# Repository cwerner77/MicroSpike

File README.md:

# µSpike
An analog spiking neural network (SNN) experiment board with digital control

## Purpose
A powerful and flexible experimental board for exploring SNN technology. This project is primarily aimed at lecturers, students, and researchers at universities.

## Project parts
- Electronics: Schematics and PCB design
- Microcontroller programs usable with https://www.pjrc.com/store/teensy41.html and 
- Circuit simulation usable with https://www.falstad.com/circuit/

## Prerequisites
- Basic knowledge on how SNN work
- Basic skills in hardware-level computer engineering: setting up microcontrollers and attaching sensors as needed
- Basic skills in electrical engineering: use a graphical circuit simulation tool for designing a SNN circuit from predefined building blocks

## Typical workflow
1. Design your SNN in simulation environment
2. Build µSpike board and flash µSpike control software
3. Configure µSpike to your application's needs using the µSpike control software
4. Do your experiments and enjoy µSpike control software's powerful logging features

## Licenses
- All hardware parts: CERN-OHL-P-2.0
- All software parts: Apache-2.0 license

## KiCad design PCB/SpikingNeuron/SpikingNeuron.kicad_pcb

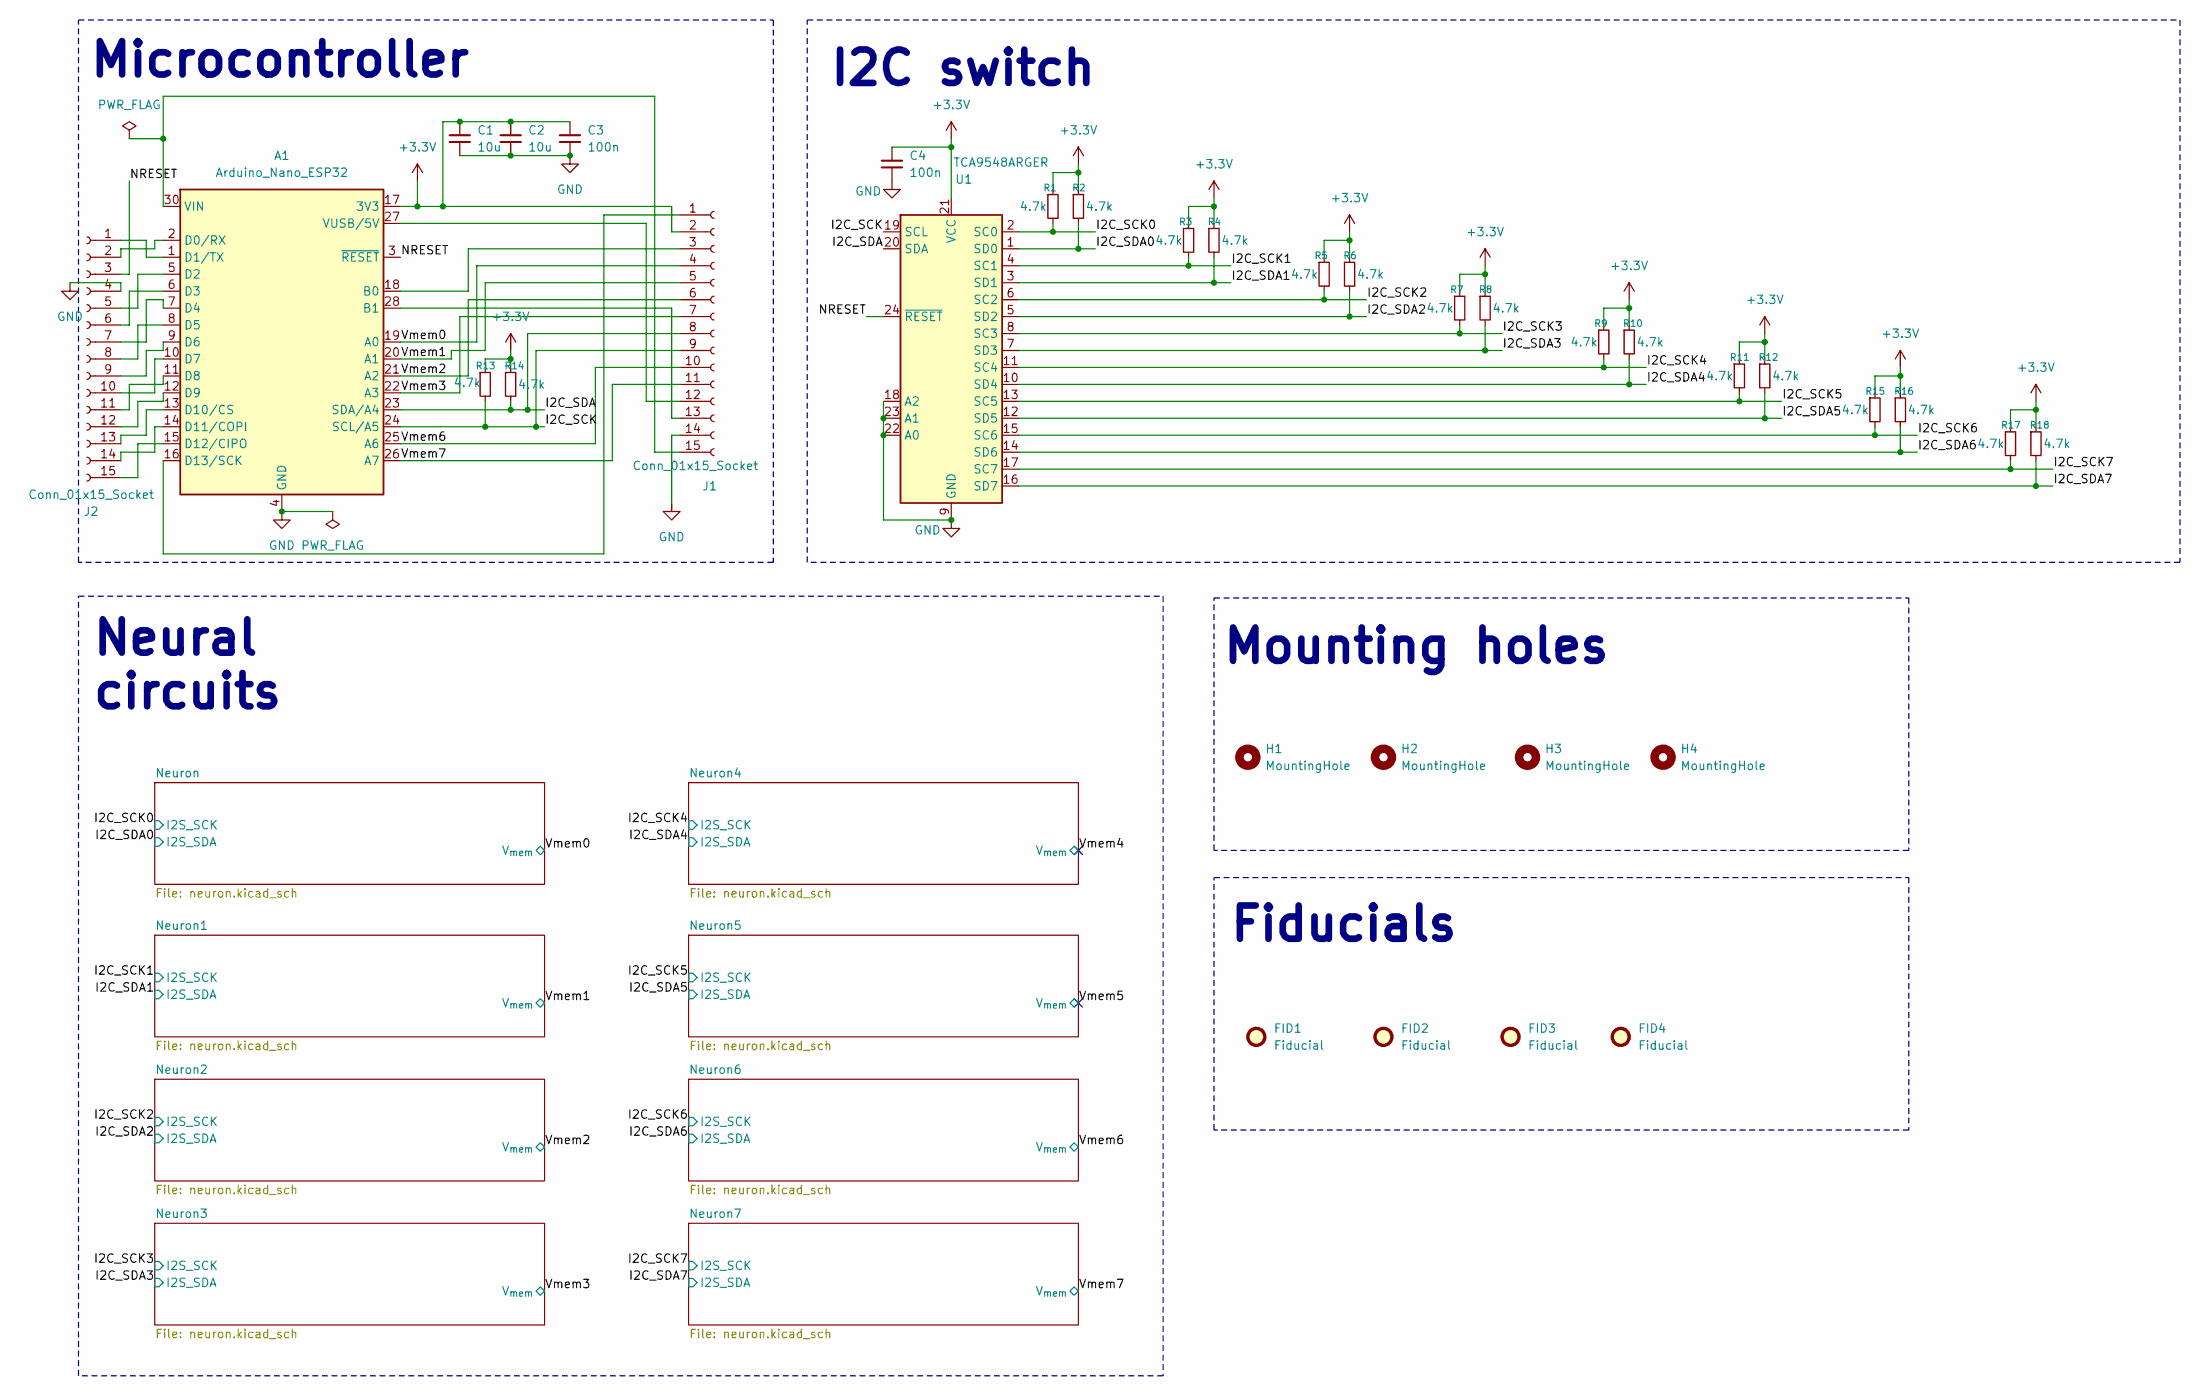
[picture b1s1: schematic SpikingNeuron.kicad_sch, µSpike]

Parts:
A1: Arduino_Nano_ESP32; Arduino_Nano
C1, C2: 10u; C_0603_1608Metric_Pad1.08x0.95mm_HandSolder
C3, C4: 100n; C_0402_1005Metric_Pad0.74x0.62mm_HandSolder
FID1, FID2, FID3, FID4: Fiducial; Fiducial_0.75mm_Mask1.5mm
H1, H2, H3, H4: MountingHole; MountingHole_3.2mm_M3
J1, J2: Conn_01x15_Socket; PinSocket_1x15_P2.54mm_Vertical
R1, R2, R3, R4, R5, R6, R7, R8, R9, R10, R11, R12, R13, R14, R15, R16, R17, R18: 4.7k; R_0402_1005Metric_Pad0.72x0.64mm_HandSolder
U1: TCA9548ARGER; Texas_RGE0024C_VQFN-24-1EP_4x4mm_P0.5mm_EP2.1x2.1mm

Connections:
+3.3V: A1.17 (3V3), C1.1, C2.1, C3.1, C4.1, J1.2, R1.1, R2.1, R3.1, R4.1, R5.1, R6.1, R7.1, R8.1, R9.1, R10.1, R11.1, R12.1, R13.1, R14.1, R15.1, R16.1, R17.1, R18.1, U1.21 (VCC); also elsewhere on the board
/I2C_SCK: A1.24 (SCL/A5), J1.9, R13.2, U1.19 (SCL)
/I2C_SCK0: R1.2, U1.2 (SC0); also elsewhere on the board
/I2C_SCK1: R3.2, U1.4 (SC1); also elsewhere on the board
/I2C_SCK2: R5.2, U1.6 (SC2); also elsewhere on the board
/I2C_SCK3: R7.2, U1.8 (SC3); also elsewhere on the board
/I2C_SCK4: R9.2, U1.11 (SC4); also elsewhere on the board
/I2C_SCK5: R11.2, U1.13 (SC5); also elsewhere on the board
/I2C_SCK6: R15.2, U1.15 (SC6); also elsewhere on the board
/I2C_SCK7: R17.2, U1.17 (SC7); also elsewhere on the board
/I2C_SDA: A1.23 (SDA/A4), J1.8, R14.2, U1.20 (SDA)
/I2C_SDA0: R2.2, U1.1 (SD0); also elsewhere on the board
/I2C_SDA1: R4.2, U1.3 (SD1); also elsewhere on the board
/I2C_SDA2: R6.2, U1.5 (SD2); also elsewhere on the board
/I2C_SDA3: R8.2, U1.7 (SD3); also elsewhere on the board
/I2C_SDA4: R10.2, U1.10 (SD4); also elsewhere on the board
/I2C_SDA5: R12.2, U1.12 (SD5); also elsewhere on the board
/I2C_SDA6: R16.2, U1.14 (SD6); also elsewhere on the board
/I2C_SDA7: R18.2, U1.16 (SD7); also elsewhere on the board
/NRESET: A1.3 (~RESET), J2.3, U1.24 (~RESET)
/Vmem0: A1.19 (A0), J1.4; also elsewhere on the board
/Vmem1: A1.20 (A1), J1.5; also elsewhere on the board
/Vmem2: A1.21 (A2), J1.6; also elsewhere on the board
/Vmem3: A1.22 (A3), J1.7; also elsewhere on the board
/Vmem6: A1.25 (A6), J1.10; also elsewhere on the board
/Vmem7: A1.26 (A7), J1.11; also elsewhere on the board
GND: A1.4 (GND), A1.29 (GND), C1.2, C2.2, C3.2, C4.2, J1.14, J2.4, U1.9 (GND), U1.18 (A2), U1.22 (A0), U1.23 (A1); also elsewhere on the board
unnamed: A1.18 (B0), J1.3
unnamed: A1.28 (B1), J1.13
unnamed: A1.2 (D0/RX), J2.2
unnamed: A1.1 (D1/TX), J2.1
unnamed: A1.5 (D2), J2.5
unnamed: A1.6 (D3), J2.6
unnamed: A1.7 (D4), J2.7
unnamed: A1.8 (D5), J2.8
unnamed: A1.9 (D6), J2.9
unnamed: A1.10 (D7), J2.10
unnamed: A1.11 (D8), J2.11
unnamed: A1.12 (D9), J2.12
unnamed: A1.13 (D10/CS), J2.13
unnamed: A1.14 (D11/COPI), J2.14
unnamed: A1.15 (D12/CIPO), J2.15
unnamed: A1.16 (D13/SCK), J1.1
unnamed: A1.30 (VIN), J1.15
unnamed: A1.27 (VUSB/5V), J1.12

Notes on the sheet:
I2C switch
Fiducials
Neural circuits
Mounting holes
Microcontroller

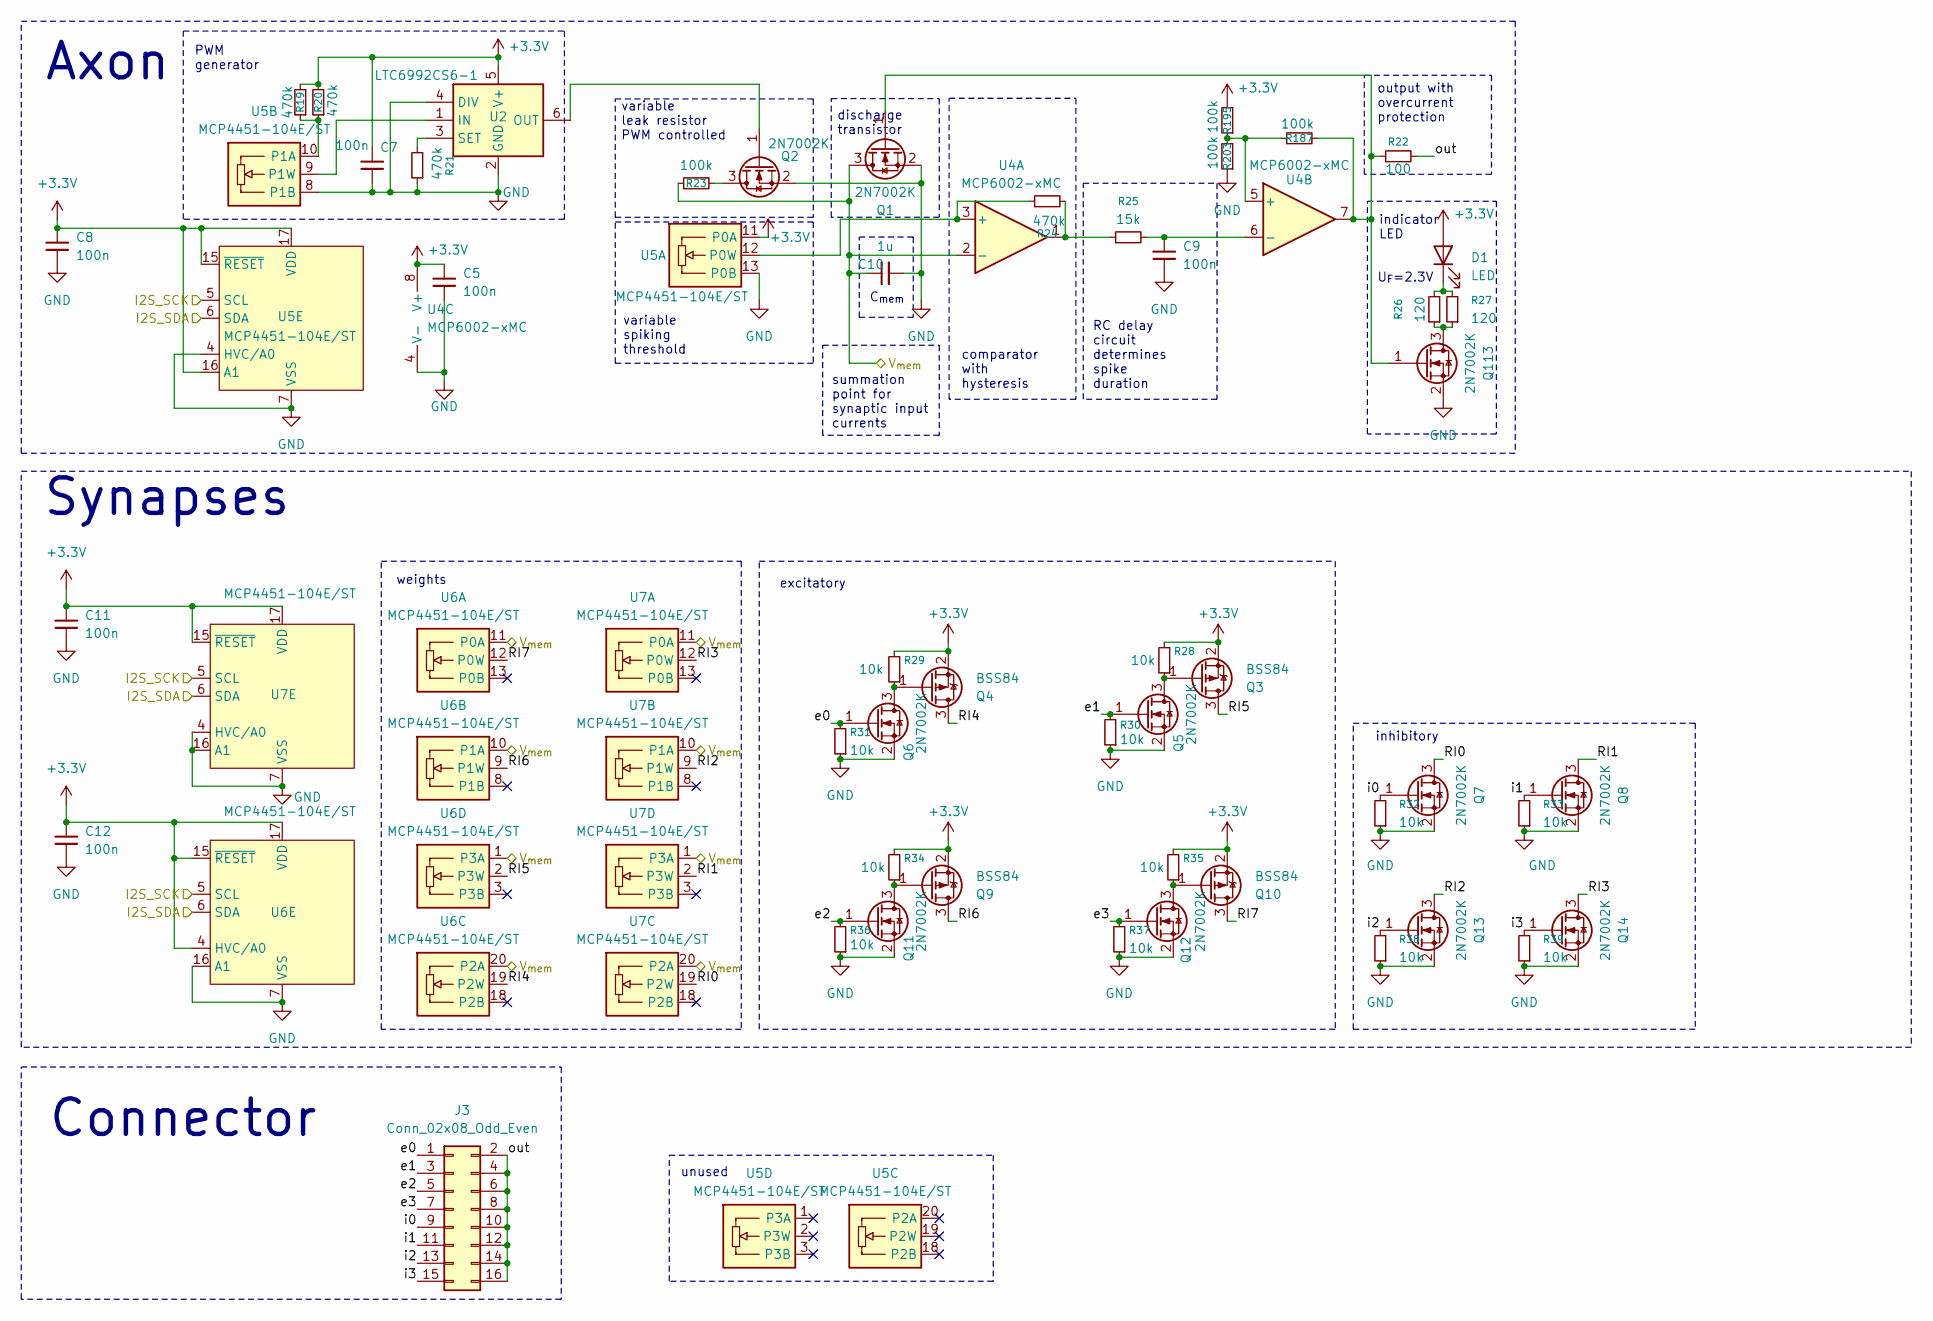
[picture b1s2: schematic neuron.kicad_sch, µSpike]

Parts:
C5, C7, C8, C9, C11, C12: 100n; C_0402_1005Metric_Pad0.74x0.62mm_HandSolder
C10: 1u; C_0402_1005Metric_Pad0.74x0.62mm_HandSolder
D1: LED; LED_1206_3216Metric_Pad1.42x1.75mm_HandSolder
J3: Conn_02x08_Odd_Even; PinSocket_2x08_P2.54mm_Vertical_SMD
Q1, Q2, Q5, Q6, Q7, Q8, Q11, Q12, Q13, Q14, Q113: 2N7002K; SOT-23
Q3, Q4, Q9, Q10: BSS84; SOT-23
R19, R20, R21, R24: 470k; R_0402_1005Metric_Pad0.72x0.64mm_HandSolder
R22: 100; R_0402_1005Metric_Pad0.72x0.64mm_HandSolder
R23, R187, R195, R203: 100k; R_0402_1005Metric_Pad0.72x0.64mm_HandSolder
R25: 15k; R_0402_1005Metric_Pad0.72x0.64mm_HandSolder
R26, R27: 120; R_0402_1005Metric_Pad0.72x0.64mm_HandSolder
R28, R29, R30, R31, R32, R33, R34, R35, R36, R37, R38, R39: 10k; R_0402_1005Metric_Pad0.72x0.64mm_HandSolder
U2: LTC6992CS6-1; TSOT-23-6
U4: MCP6002-xMC; DFN-8-1EP_3x2mm_P0.5mm_EP1.75x1.45mm
U5, U6, U7: MCP4451-104E/ST; TSSOP-20_4.4x6.5mm_P0.65mm

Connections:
+3.3V: C5.1, C7.1, C8.1, C11.1, C12.1, D1.2 (A), Q3.2 (S), Q4.2 (S), Q9.2 (S), Q10.2 (S), R19.2, R20.2, R28.2, R29.2, R34.2, R35.2, R195.2, U2.5 (V+), U4.8 (V+), U5.11 (P0A), U5.15 (~RESET), U5.16 (A1), U5.17 (VDD), U6.4 (HVC/A0), U6.15 (~RESET), U6.17 (VDD), U7.15 (~RESET), U7.17 (VDD); also elsewhere on the board
/I2C_SCK0: U5.5 (SCL), U6.5 (SCL), U7.5 (SCL); also elsewhere on the board
/I2C_SDA0: U5.6 (SDA), U6.6 (SDA), U7.6 (SDA); also elsewhere on the board
/Neuron/RI0: Q7.3 (D), U7.19 (P2W)
/Neuron/RI1: Q8.3 (D), U7.2 (P3W)
/Neuron/RI2: Q13.3 (D), U7.9 (P1W)
/Neuron/RI3: Q14.3 (D), U7.12 (P0W)
/Neuron/RI4: Q4.3 (D), U6.19 (P2W)
/Neuron/RI5: Q3.3 (D), U6.2 (P3W)
/Neuron/RI6: Q9.3 (D), U6.9 (P1W)
/Neuron/RI7: Q10.3 (D), U6.12 (P0W)
/Neuron/e0: J3.1, Q6.1 (G), R31.2
/Neuron/e1: J3.3, Q5.1 (G), R30.2
/Neuron/e2: J3.5, Q11.1 (G), R36.2
/Neuron/e3: J3.7, Q12.1 (G), R37.2
/Neuron/i0: J3.9, Q7.1 (G), R32.2
/Neuron/i1: J3.11, Q8.1 (G), R33.2
/Neuron/i2: J3.13, Q13.1 (G), R38.2
/Neuron/i3: J3.15, Q14.1 (G), R39.2
/Neuron/out: J3.2, J3.4, J3.6, J3.8, J3.10, J3.12, J3.14, J3.16, R22.2
/Vmem0: C10.1, Q1.3 (D), R23.1, U4.2 (-), U6.1 (P3A), U6.10 (P1A), U6.11 (P0A), U6.20 (P2A), U7.1 (P3A), U7.10 (P1A), U7.11 (P0A), U7.20 (P2A); also elsewhere on the board
GND: C5.2, C7.2, C8.2, C9.1, C10.2, C11.2, C12.2, Q1.2 (S), Q2.2 (S), Q5.2 (S), Q6.2 (S), Q7.2 (S), Q8.2 (S), Q11.2 (S), Q12.2 (S), Q13.2 (S), Q14.2 (S), Q113.2 (S), R21.1, R30.1, R31.1, R32.1, R33.1, R36.1, R37.1, R38.1, R39.1, R203.1, U2.2 (GND), U2.4 (DIV), U4.4 (V-), U4.9 (V-), U5.4 (HVC/A0), U5.7 (VSS), U5.8 (P1B), U5.13 (P0B), U6.7 (VSS), U6.16 (A1), U7.4 (HVC/A0), U7.7 (VSS), U7.16 (A1); also elsewhere on the board
unnamed: D1.1 (K), R26.2, R27.2
unnamed: Q1.1 (G), Q113.1 (G), R22.1, R187.2, U4.7
unnamed: Q2.3 (D), R23.2
unnamed: Q2.1 (G), U2.6 (OUT)
unnamed: Q3.1 (G), Q5.3 (D), R28.1
unnamed: Q4.1 (G), Q6.3 (D), R29.1
unnamed: Q10.1 (G), Q12.3 (D), R35.1
unnamed: Q9.1 (G), Q11.3 (D), R34.1
unnamed: Q113.3 (D), R26.1, R27.1
unnamed: R24.2, R25.1, U4.1
unnamed: U2.1 (IN), U5.9 (P1W)
unnamed: R21.2, U2.3 (SET)
unnamed: R24.1, U4.3 (+), U5.12 (P0W)
unnamed: R187.1, R195.1, R203.2, U4.5 (+)
unnamed: C9.2, R25.2, U4.6 (-)
unnamed: R19.1, R20.1, U5.10 (P1A)

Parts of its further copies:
C13, C15, C16, C17, C19, C20, C21, C23, C24, C25, C27, C28, C29, C31, C32, C33, C35, C36, C37, C39, C40, C41, C43, C44, C45, C47, C48, C49, C51, C52, C53, C55, C56, C57, C59, C60, C61, C63, C64, C65, C67, C68: 100n; C_0402_1005Metric_Pad0.74x0.62mm_HandSolder
C18, C26, C34, C42, C50, C58, C66: 1u; C_0402_1005Metric_Pad0.74x0.62mm_HandSolder
D2, D3, D4, D5, D6, D7, D8: LED; LED_1206_3216Metric_Pad1.42x1.75mm_HandSolder
J4, J5, J6, J7, J8, J9, J10: Conn_02x08_Odd_Even; PinSocket_2x08_P2.54mm_Vertical_SMD
Q15, Q16, Q19, Q20, Q21, Q22, Q25, Q26, Q27, Q28, Q29, Q30, Q33, Q34, Q35, Q36, Q39, Q40, Q41, Q42, Q43, Q44, Q47, Q48, Q49, Q50, Q53, Q54, Q55, Q56, Q57, Q58, Q61, Q62, Q63, Q64, Q67, Q68, Q69, Q70, Q71, Q72, Q75, Q76, Q77, Q78, Q81, Q82, Q83, Q84, Q85, Q86, Q89, Q90, Q91, Q92, Q95, Q96, Q97, Q98, Q99, Q100, Q103, Q104, Q105, Q106, Q109, Q110, Q111, Q112, Q114, Q115, Q116, Q117, Q118, Q119, Q120: 2N7002K; SOT-23
Q17, Q18, Q23, Q24, Q31, Q32, Q37, Q38, Q45, Q46, Q51, Q52, Q59, Q60, Q65, Q66, Q73, Q74, Q79, Q80, Q87, Q88, Q93, Q94, Q101, Q102, Q107, Q108: BSS84; SOT-23
R40, R41, R42, R45, R61, R62, R63, R66, R82, R83, R84, R87, R103, R104, R105, R108, R124, R125, R126, R129, R145, R146, R147, R150, R166, R167, R168, R171: 470k; R_0402_1005Metric_Pad0.72x0.64mm_HandSolder
R43, R64, R85, R106, R127, R148, R169: 100; R_0402_1005Metric_Pad0.72x0.64mm_HandSolder
R44, R65, R86, R107, R128, R149, R170, R188, R189, R190, R191, R192, R193, R194, R196, R197, R198, R199, R200, R201, R202, R204, R205, R206, R207, R208, R209, R210: 100k; R_0402_1005Metric_Pad0.72x0.64mm_HandSolder
R46, R67, R88, R109, R130, R151, R172: 15k; R_0402_1005Metric_Pad0.72x0.64mm_HandSolder
R47, R48, R68, R69, R89, R90, R110, R111, R131, R132, R152, R153, R173, R174: 120; R_0402_1005Metric_Pad0.72x0.64mm_HandSolder
R49, R50, R51, R52, R53, R54, R55, R56, R57, R58, R59, R60, R70, R71, R72, R73, R74, R75, R76, R77, R78, R79, R80, R81, R91, R92, R93, R94, R95, R96, R97, R98, R99, R100, R101, R102, R112, R113, R114, R115, R116, R117, R118, R119, R120, R121, R122, R123, R133, R134, R135, R136, R137, R138, R139, R140, R141, R142, R143, R144, R154, R155, R156, R157, R158, R159, R160, R161, R162, R163, R164, R165, R175, R176, R177, R178, R179, R180, R181, R182, R183, R184, R185, R186: 10k; R_0402_1005Metric_Pad0.72x0.64mm_HandSolder
U8, U15, U22, U29, U36, U43, U50: LTC6992CS6-1; TSOT-23-6
U10, U17, U24, U31, U38, U45, U52: MCP6002-xMC; DFN-8-1EP_3x2mm_P0.5mm_EP1.75x1.45mm
U11, U12, U13, U14, U18, U19, U20, U21, U25, U26, U27, U28, U32, U34, U35, U41, U42, U48, U49, U55, U56: MCP4451-104E/ST; TSSOP-20_4.4x6.5mm_P0.65mm

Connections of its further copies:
+3.3V: C13.1, C15.1, C16.1, C19.1, C20.1, C21.1, C23.1, C24.1, C27.1, C28.1, C29.1, C31.1, C32.1, C35.1, C36.1, C37.1, C39.1, C40.1, C43.1, C44.1, C45.1, C47.1, C48.1, C51.1, C52.1, C53.1, C55.1, C56.1, C59.1, C60.1, C61.1, C63.1, C64.1, C67.1, C68.1, D2.2 (A), D3.2 (A), D4.2 (A), D5.2 (A), D6.2 (A), D7.2 (A), D8.2 (A), Q17.2 (S), Q18.2 (S), Q23.2 (S), Q24.2 (S), Q31.2 (S), Q32.2 (S), Q37.2 (S), Q38.2 (S), Q45.2 (S), Q46.2 (S), Q51.2 (S), Q52.2 (S), Q59.2 (S), Q60.2 (S), Q65.2 (S), Q66.2 (S), Q73.2 (S), Q74.2 (S), Q79.2 (S), Q80.2 (S), Q87.2 (S), Q88.2 (S), Q93.2 (S), Q94.2 (S), Q101.2 (S), Q102.2 (S), Q107.2 (S), Q108.2 (S), R40.2, R41.2, R49.2, R50.2, R55.2, R56.2, R61.2, R62.2, R70.2, R71.2, R76.2, R77.2, R82.2, R83.2, R91.2, R92.2, R97.2, R98.2, R103.2, R104.2, R112.2, R113.2, R118.2, R119.2, R124.2, R125.2, R133.2, R134.2, R139.2, R140.2, R145.2, R146.2, R154.2, R155.2, R160.2, R161.2, R166.2, R167.2, R175.2, R176.2, R181.2, R182.2, R196.2, R197.2, R198.2, R199.2, R200.2, R201.2, R202.2, U8.5 (V+), U10.8 (V+), U11.11 (P0A), U11.15 (~RESET), U11.16 (A1), U11.17 (VDD), U12.11 (P0A), U12.15 (~RESET), U12.16 (A1), U12.17 (VDD), U13.4 (HVC/A0), U13.15 (~RESET), U13.17 (VDD), U14.15 (~RESET), U14.17 (VDD), U15.5 (V+), U17.8 (V+), U18.11 (P0A), U18.15 (~RESET), U18.16 (A1), U18.17 (VDD), U19.11 (P0A), U19.15 (~RESET), U19.16 (A1), U19.17 (VDD), U20.4 (HVC/A0), U20.15 (~RESET), U20.17 (VDD), U21.15 (~RESET), U21.17 (VDD), U22.5 (V+), U24.8 (V+), U25.11 (P0A), U25.15 (~RESET), U25.16 (A1), U25.17 (VDD), U26.11 (P0A), U26.15 (~RESET), U26.16 (A1), U26.17 (VDD), U27.4 (HVC/A0), U27.15 (~RESET), U27.17 (VDD), U28.15 (~RESET), U28.17 (VDD), U29.5 (V+), U31.8 (V+), U32.11 (P0A), U32.15 (~RESET), U32.16 (A1), U32.17 (VDD), U34.4 (HVC/A0), U34.15 (~RESET), U34.17 (VDD), U35.15 (~RESET), U35.17 (VDD), U36.5 (V+), U38.8 (V+), U41.4 (HVC/A0), U41.15 (~RESET), U41.17 (VDD), U42.15 (~RESET), U42.17 (VDD), U43.5 (V+), U45.8 (V+), U48.4 (HVC/A0), U48.15 (~RESET), U48.17 (VDD), U49.15 (~RESET), U49.17 (VDD), U50.5 (V+), U52.8 (V+), U55.4 (HVC/A0), U55.15 (~RESET), U55.17 (VDD), U56.15 (~RESET), U56.17 (VDD); also elsewhere on the board
/I2C_SCK1: U11.5 (SCL), U13.5 (SCL), U14.5 (SCL); also elsewhere on the board
/I2C_SCK2: U12.5 (SCL), U20.5 (SCL), U21.5 (SCL); also elsewhere on the board
/I2C_SCK3: U18.5 (SCL), U27.5 (SCL), U28.5 (SCL); also elsewhere on the board
/I2C_SCK4: U19.5 (SCL), U34.5 (SCL), U35.5 (SCL); also elsewhere on the board
/I2C_SCK5: U25.5 (SCL), U41.5 (SCL), U42.5 (SCL); also elsewhere on the board
/I2C_SCK6: U26.5 (SCL), U48.5 (SCL), U49.5 (SCL); also elsewhere on the board
/I2C_SCK7: U32.5 (SCL), U55.5 (SCL), U56.5 (SCL); also elsewhere on the board
/I2C_SDA1: U11.6 (SDA), U13.6 (SDA), U14.6 (SDA); also elsewhere on the board
/I2C_SDA2: U12.6 (SDA), U20.6 (SDA), U21.6 (SDA); also elsewhere on the board
/I2C_SDA3: U18.6 (SDA), U27.6 (SDA), U28.6 (SDA); also elsewhere on the board
/I2C_SDA4: U19.6 (SDA), U34.6 (SDA), U35.6 (SDA); also elsewhere on the board
/I2C_SDA5: U25.6 (SDA), U41.6 (SDA), U42.6 (SDA); also elsewhere on the board
/I2C_SDA6: U26.6 (SDA), U48.6 (SDA), U49.6 (SDA); also elsewhere on the board
/I2C_SDA7: U32.6 (SDA), U55.6 (SDA), U56.6 (SDA); also elsewhere on the board
/Neuron1/RI0: Q21.3 (D), U14.19 (P2W)
/Neuron1/RI1: Q22.3 (D), U14.2 (P3W)
/Neuron1/RI2: Q27.3 (D), U14.9 (P1W)
/Neuron1/RI3: Q28.3 (D), U14.12 (P0W)
/Neuron1/RI4: Q18.3 (D), U13.19 (P2W)
/Neuron1/RI5: Q17.3 (D), U13.2 (P3W)
/Neuron1/RI6: Q23.3 (D), U13.9 (P1W)
/Neuron1/RI7: Q24.3 (D), U13.12 (P0W)
/Neuron1/e0: J4.1, Q20.1 (G), R52.2
/Neuron1/e1: J4.3, Q19.1 (G), R51.2
/Neuron1/e2: J4.5, Q25.1 (G), R57.2
/Neuron1/e3: J4.7, Q26.1 (G), R58.2
/Neuron1/i0: J4.9, Q21.1 (G), R53.2
/Neuron1/i1: J4.11, Q22.1 (G), R54.2
/Neuron1/i2: J4.13, Q27.1 (G), R59.2
/Neuron1/i3: J4.15, Q28.1 (G), R60.2
/Neuron1/out: J4.2, J4.4, J4.6, J4.8, J4.10, J4.12, J4.14, J4.16, R43.2
/Neuron2/RI0: Q35.3 (D), U21.19 (P2W)
/Neuron2/RI1: Q36.3 (D), U21.2 (P3W)
/Neuron2/RI2: Q41.3 (D), U21.9 (P1W)
/Neuron2/RI3: Q42.3 (D), U21.12 (P0W)
/Neuron2/RI4: Q32.3 (D), U20.19 (P2W)
/Neuron2/RI5: Q31.3 (D), U20.2 (P3W)
/Neuron2/RI6: Q37.3 (D), U20.9 (P1W)
/Neuron2/RI7: Q38.3 (D), U20.12 (P0W)
/Neuron2/e0: J5.1, Q34.1 (G), R73.2
/Neuron2/e1: J5.3, Q33.1 (G), R72.2
/Neuron2/e2: J5.5, Q39.1 (G), R78.2
/Neuron2/e3: J5.7, Q40.1 (G), R79.2
/Neuron2/i0: J5.9, Q35.1 (G), R74.2
/Neuron2/i1: J5.11, Q36.1 (G), R75.2
/Neuron2/i2: J5.13, Q41.1 (G), R80.2
/Neuron2/i3: J5.15, Q42.1 (G), R81.2
/Neuron2/out: J5.2, J5.4, J5.6, J5.8, J5.10, J5.12, J5.14, J5.16, R64.2
/Neuron3/RI0: Q49.3 (D), U28.19 (P2W)
/Neuron3/RI1: Q50.3 (D), U28.2 (P3W)
/Neuron3/RI2: Q55.3 (D), U28.9 (P1W)
/Neuron3/RI3: Q56.3 (D), U28.12 (P0W)
/Neuron3/RI4: Q46.3 (D), U27.19 (P2W)
/Neuron3/RI5: Q45.3 (D), U27.2 (P3W)
/Neuron3/RI6: Q51.3 (D), U27.9 (P1W)
/Neuron3/RI7: Q52.3 (D), U27.12 (P0W)
/Neuron3/e0: J6.1, Q48.1 (G), R94.2
/Neuron3/e1: J6.3, Q47.1 (G), R93.2
/Neuron3/e2: J6.5, Q53.1 (G), R99.2
/Neuron3/e3: J6.7, Q54.1 (G), R100.2
/Neuron3/i0: J6.9, Q49.1 (G), R95.2
/Neuron3/i1: J6.11, Q50.1 (G), R96.2
/Neuron3/i2: J6.13, Q55.1 (G), R101.2
/Neuron3/i3: J6.15, Q56.1 (G), R102.2
/Neuron3/out: J6.2, J6.4, J6.6, J6.8, J6.10, J6.12, J6.14, J6.16, R85.2
/Neuron4/RI0: Q63.3 (D), U35.19 (P2W)
/Neuron4/RI1: Q64.3 (D), U35.2 (P3W)
/Neuron4/RI2: Q69.3 (D), U35.9 (P1W)
/Neuron4/RI3: Q70.3 (D), U35.12 (P0W)
/Neuron4/RI4: Q60.3 (D), U34.19 (P2W)
/Neuron4/RI5: Q59.3 (D), U34.2 (P3W)
/Neuron4/RI6: Q65.3 (D), U34.9 (P1W)
/Neuron4/RI7: Q66.3 (D), U34.12 (P0W)
/Neuron4/e0: J7.1, Q62.1 (G), R115.2
/Neuron4/e1: J7.3, Q61.1 (G), R114.2
/Neuron4/e2: J7.5, Q67.1 (G), R120.2
/Neuron4/e3: J7.7, Q68.1 (G), R121.2
/Neuron4/i0: J7.9, Q63.1 (G), R116.2
/Neuron4/i1: J7.11, Q64.1 (G), R117.2
/Neuron4/i2: J7.13, Q69.1 (G), R122.2
/Neuron4/i3: J7.15, Q70.1 (G), R123.2
/Neuron4/out: J7.2, J7.4, J7.6, J7.8, J7.10, J7.12, J7.14, J7.16, R106.2
/Neuron5/RI0: Q77.3 (D), U42.19 (P2W)
/Neuron5/RI1: Q78.3 (D), U42.2 (P3W)
/Neuron5/RI2: Q83.3 (D), U42.9 (P1W)
/Neuron5/RI3: Q84.3 (D), U42.12 (P0W)
/Neuron5/RI4: Q74.3 (D), U41.19 (P2W)
/Neuron5/RI5: Q73.3 (D), U41.2 (P3W)
/Neuron5/RI6: Q79.3 (D), U41.9 (P1W)
/Neuron5/RI7: Q80.3 (D), U41.12 (P0W)
/Neuron5/e0: J8.1, Q76.1 (G), R136.2
/Neuron5/e1: J8.3, Q75.1 (G), R135.2
/Neuron5/e2: J8.5, Q81.1 (G), R141.2
/Neuron5/e3: J8.7, Q82.1 (G), R142.2
/Neuron5/i0: J8.9, Q77.1 (G), R137.2
/Neuron5/i1: J8.11, Q78.1 (G), R138.2
/Neuron5/i2: J8.13, Q83.1 (G), R143.2
/Neuron5/i3: J8.15, Q84.1 (G), R144.2
/Neuron5/out: J8.2, J8.4, J8.6, J8.8, J8.10, J8.12, J8.14, J8.16, R127.2
/Neuron6/RI0: Q91.3 (D), U49.19 (P2W)
/Neuron6/RI1: Q92.3 (D), U49.2 (P3W)
/Neuron6/RI2: Q97.3 (D), U49.9 (P1W)
/Neuron6/RI3: Q98.3 (D), U49.12 (P0W)
/Neuron6/RI4: Q88.3 (D), U48.19 (P2W)
/Neuron6/RI5: Q87.3 (D), U48.2 (P3W)
/Neuron6/RI6: Q93.3 (D), U48.9 (P1W)
/Neuron6/RI7: Q94.3 (D), U48.12 (P0W)
/Neuron6/e0: J9.1, Q90.1 (G), R157.2
/Neuron6/e1: J9.3, Q89.1 (G), R156.2
/Neuron6/e2: J9.5, Q95.1 (G), R162.2
/Neuron6/e3: J9.7, Q96.1 (G), R163.2
/Neuron6/i0: J9.9, Q91.1 (G), R158.2
/Neuron6/i1: J9.11, Q92.1 (G), R159.2
/Neuron6/i2: J9.13, Q97.1 (G), R164.2
/Neuron6/i3: J9.15, Q98.1 (G), R165.2
/Neuron6/out: J9.2, J9.4, J9.6, J9.8, J9.10, J9.12, J9.14, J9.16, R148.2
/Neuron7/RI0: Q105.3 (D), U56.19 (P2W)
/Neuron7/RI1: Q106.3 (D), U56.2 (P3W)
/Neuron7/RI2: Q111.3 (D), U56.9 (P1W)
/Neuron7/RI3: Q112.3 (D), U56.12 (P0W)
/Neuron7/RI4: Q102.3 (D), U55.19 (P2W)
/Neuron7/RI5: Q101.3 (D), U55.2 (P3W)
/Neuron7/RI6: Q107.3 (D), U55.9 (P1W)
/Neuron7/RI7: Q108.3 (D), U55.12 (P0W)
/Neuron7/e0: J10.1, Q104.1 (G), R178.2
/Neuron7/e1: J10.3, Q103.1 (G), R177.2
/Neuron7/e2: J10.5, Q109.1 (G), R183.2
/Neuron7/e3: J10.7, Q110.1 (G), R184.2
/Neuron7/i0: J10.9, Q105.1 (G), R179.2
/Neuron7/i1: J10.11, Q106.1 (G), R180.2
/Neuron7/i2: J10.13, Q111.1 (G), R185.2
/Neuron7/i3: J10.15, Q112.1 (G), R186.2
/Neuron7/out: J10.2, J10.4, J10.6, J10.8, J10.10, J10.12, J10.14, J10.16, R169.2
/Vmem1: C18.1, Q15.3 (D), R44.1, U10.2 (-), U13.1 (P3A), U13.10 (P1A), U13.11 (P0A), U13.20 (P2A), U14.1 (P3A), U14.10 (P1A), U14.11 (P0A), U14.20 (P2A); also elsewhere on the board
/Vmem2: C26.1, Q29.3 (D), R65.1, U17.2 (-), U20.1 (P3A), U20.10 (P1A), U20.11 (P0A), U20.20 (P2A), U21.1 (P3A), U21.10 (P1A), U21.11 (P0A), U21.20 (P2A); also elsewhere on the board
/Vmem3: C34.1, Q43.3 (D), R86.1, U24.2 (-), U27.1 (P3A), U27.10 (P1A), U27.11 (P0A), U27.20 (P2A), U28.1 (P3A), U28.10 (P1A), U28.11 (P0A), U28.20 (P2A); also elsewhere on the board
/Vmem4: C42.1, Q57.3 (D), R107.1, U31.2 (-), U34.1 (P3A), U34.10 (P1A), U34.11 (P0A), U34.20 (P2A), U35.1 (P3A), U35.10 (P1A), U35.11 (P0A), U35.20 (P2A)
/Vmem5: C50.1, Q71.3 (D), R128.1, U38.2 (-), U41.1 (P3A), U41.10 (P1A), U41.11 (P0A), U41.20 (P2A), U42.1 (P3A), U42.10 (P1A), U42.11 (P0A), U42.20 (P2A)
/Vmem6: C58.1, Q85.3 (D), R149.1, U45.2 (-), U48.1 (P3A), U48.10 (P1A), U48.11 (P0A), U48.20 (P2A), U49.1 (P3A), U49.10 (P1A), U49.11 (P0A), U49.20 (P2A); also elsewhere on the board
/Vmem7: C66.1, Q99.3 (D), R170.1, U52.2 (-), U55.1 (P3A), U55.10 (P1A), U55.11 (P0A), U55.20 (P2A), U56.1 (P3A), U56.10 (P1A), U56.11 (P0A), U56.20 (P2A); also elsewhere on the board
GND: C13.2, C15.2, C16.2, C17.1, C18.2, C19.2, C20.2, C21.2, C23.2, C24.2, C25.1, C26.2, C27.2, C28.2, C29.2, C31.2, C32.2, C33.1, C34.2, C35.2, C36.2, C37.2, C39.2, C40.2, C41.1, C42.2, C43.2, C44.2, C45.2, C47.2, C48.2, C49.1, C50.2, C51.2, C52.2, C53.2, C55.2, C56.2, C57.1, C58.2, C59.2, C60.2, C61.2, C63.2, C64.2, C65.1, C66.2, C67.2, C68.2, Q15.2 (S), Q16.2 (S), Q19.2 (S), Q20.2 (S), Q21.2 (S), Q22.2 (S), Q25.2 (S), Q26.2 (S), Q27.2 (S), Q28.2 (S), Q29.2 (S), Q30.2 (S), Q33.2 (S), Q34.2 (S), Q35.2 (S), Q36.2 (S), Q39.2 (S), Q40.2 (S), Q41.2 (S), Q42.2 (S), Q43.2 (S), Q44.2 (S), Q47.2 (S), Q48.2 (S), Q49.2 (S), Q50.2 (S), Q53.2 (S), Q54.2 (S), Q55.2 (S), Q56.2 (S), Q57.2 (S), Q58.2 (S), Q61.2 (S), Q62.2 (S), Q63.2 (S), Q64.2 (S), Q67.2 (S), Q68.2 (S), Q69.2 (S), Q70.2 (S), Q71.2 (S), Q72.2 (S), Q75.2 (S), Q76.2 (S), Q77.2 (S), Q78.2 (S), Q81.2 (S), Q82.2 (S), Q83.2 (S), Q84.2 (S), Q85.2 (S), Q86.2 (S), Q89.2 (S), Q90.2 (S), Q91.2 (S), Q92.2 (S), Q95.2 (S), Q96.2 (S), Q97.2 (S), Q98.2 (S), Q99.2 (S), Q100.2 (S), Q103.2 (S), Q104.2 (S), Q105.2 (S), Q106.2 (S), Q109.2 (S), Q110.2 (S), Q111.2 (S), Q112.2 (S), Q114.2 (S), Q115.2 (S), Q116.2 (S), Q117.2 (S), Q118.2 (S), Q119.2 (S), Q120.2 (S), R42.1, R51.1, R52.1, R53.1, R54.1, R57.1, R58.1, R59.1, R60.1, R63.1, R72.1, R73.1, R74.1, R75.1, R78.1, R79.1, R80.1, R81.1, R84.1, R93.1, R94.1, R95.1, R96.1, R99.1, R100.1, R101.1, R102.1, R105.1, R114.1, R115.1, R116.1, R117.1, R120.1, R121.1, R122.1, R123.1, R126.1, R135.1, R136.1, R137.1, R138.1, R141.1, R142.1, R143.1, R144.1, R147.1, R156.1, R157.1, R158.1, R159.1, R162.1, R163.1, R164.1, R165.1, R168.1, R177.1, R178.1, R179.1, R180.1, R183.1, R184.1, R185.1, R186.1, R204.1, R205.1, R206.1, R207.1, R208.1, R209.1, R210.1, U8.2 (GND), U8.4 (DIV), U10.4 (V-), U10.9 (V-), U11.4 (HVC/A0), U11.7 (VSS), U11.8 (P1B), U11.13 (P0B), U12.4 (HVC/A0), U12.7 (VSS), U12.8 (P1B), U12.13 (P0B), U13.7 (VSS), U13.16 (A1), U14.4 (HVC/A0), U14.7 (VSS), U14.16 (A1), U15.2 (GND), U15.4 (DIV), U17.4 (V-), U17.9 (V-), U18.4 (HVC/A0), U18.7 (VSS), U18.8 (P1B), U18.13 (P0B), U19.4 (HVC/A0), U19.7 (VSS), U19.8 (P1B), U19.13 (P0B), U20.7 (VSS), U20.16 (A1), U21.4 (HVC/A0), U21.7 (VSS), U21.16 (A1), U22.2 (GND), U22.4 (DIV), U24.4 (V-), U24.9 (V-), U25.4 (HVC/A0), U25.7 (VSS), U25.8 (P1B), U25.13 (P0B), U26.4 (HVC/A0), U26.7 (VSS), U26.8 (P1B), U26.13 (P0B), U27.7 (VSS), U27.16 (A1), U28.4 (HVC/A0), U28.7 (VSS), U28.16 (A1), U29.2 (GND), U29.4 (DIV), U31.4 (V-), U31.9 (V-), U32.4 (HVC/A0), U32.7 (VSS), U32.8 (P1B), U32.13 (P0B), U34.7 (VSS), U34.16 (A1), U35.4 (HVC/A0), U35.7 (VSS), U35.16 (A1), U36.2 (GND), U36.4 (DIV), U38.4 (V-), U38.9 (V-), U41.7 (VSS), U41.16 (A1), U42.4 (HVC/A0), U42.7 (VSS), U42.16 (A1), U43.2 (GND), U43.4 (DIV), U45.4 (V-), U45.9 (V-), U48.7 (VSS), U48.16 (A1), U49.4 (HVC/A0), U49.7 (VSS), U49.16 (A1), U50.2 (GND), U50.4 (DIV), U52.4 (V-), U52.9 (V-), U55.7 (VSS), U55.16 (A1), U56.4 (HVC/A0), U56.7 (VSS), U56.16 (A1); also elsewhere on the board
unnamed: D2.1 (K), R47.2, R48.2
unnamed: D3.1 (K), R68.2, R69.2
unnamed: D4.1 (K), R89.2, R90.2
unnamed: D5.1 (K), R110.2, R111.2
unnamed: D6.1 (K), R131.2, R132.2
unnamed: D7.1 (K), R152.2, R153.2
unnamed: D8.1 (K), R173.2, R174.2
unnamed: Q16.3 (D), R44.2
unnamed: Q16.1 (G), U8.6 (OUT)
unnamed: Q17.1 (G), Q19.3 (D), R49.1
unnamed: Q18.1 (G), Q20.3 (D), R50.1
unnamed: Q23.1 (G), Q25.3 (D), R55.1
unnamed: Q24.1 (G), Q26.3 (D), R56.1
unnamed: Q30.3 (D), R65.2
unnamed: Q30.1 (G), U15.6 (OUT)
unnamed: Q31.1 (G), Q33.3 (D), R70.1
unnamed: Q32.1 (G), Q34.3 (D), R71.1
unnamed: Q37.1 (G), Q39.3 (D), R76.1
unnamed: Q38.1 (G), Q40.3 (D), R77.1
unnamed: Q44.3 (D), R86.2
unnamed: Q44.1 (G), U22.6 (OUT)
unnamed: Q45.1 (G), Q47.3 (D), R91.1
unnamed: Q46.1 (G), Q48.3 (D), R92.1
unnamed: Q51.1 (G), Q53.3 (D), R97.1
unnamed: Q52.1 (G), Q54.3 (D), R98.1
unnamed: Q58.3 (D), R107.2
unnamed: Q58.1 (G), U29.6 (OUT)
unnamed: Q59.1 (G), Q61.3 (D), R112.1
unnamed: Q60.1 (G), Q62.3 (D), R113.1
unnamed: Q65.1 (G), Q67.3 (D), R118.1
unnamed: Q66.1 (G), Q68.3 (D), R119.1
unnamed: Q72.3 (D), R128.2
unnamed: Q72.1 (G), U36.6 (OUT)
unnamed: Q73.1 (G), Q75.3 (D), R133.1
unnamed: Q74.1 (G), Q76.3 (D), R134.1
unnamed: Q79.1 (G), Q81.3 (D), R139.1
unnamed: Q80.1 (G), Q82.3 (D), R140.1
unnamed: Q86.3 (D), R149.2
unnamed: Q86.1 (G), U43.6 (OUT)
unnamed: Q87.1 (G), Q89.3 (D), R154.1
unnamed: Q88.1 (G), Q90.3 (D), R155.1
unnamed: Q93.1 (G), Q95.3 (D), R160.1
unnamed: Q94.1 (G), Q96.3 (D), R161.1
unnamed: Q100.3 (D), R170.2
unnamed: Q100.1 (G), U50.6 (OUT)
unnamed: Q101.1 (G), Q103.3 (D), R175.1
unnamed: Q102.1 (G), Q104.3 (D), R176.1
unnamed: Q107.1 (G), Q109.3 (D), R181.1
unnamed: Q108.1 (G), Q110.3 (D), R182.1
unnamed: Q114.3 (D), R47.1, R48.1
unnamed: Q15.1 (G), Q114.1 (G), R43.1, R188.2, U10.7
unnamed: Q115.3 (D), R68.1, R69.1
unnamed: Q29.1 (G), Q115.1 (G), R64.1, R189.2, U17.7
unnamed: Q116.3 (D), R89.1, R90.1
unnamed: Q43.1 (G), Q116.1 (G), R85.1, R190.2, U24.7
unnamed: Q117.3 (D), R110.1, R111.1
unnamed: Q57.1 (G), Q117.1 (G), R106.1, R191.2, U31.7
unnamed: Q118.3 (D), R131.1, R132.1
unnamed: Q71.1 (G), Q118.1 (G), R127.1, R192.2, U38.7
unnamed: Q119.3 (D), R152.1, R153.1
unnamed: Q85.1 (G), Q119.1 (G), R148.1, R193.2, U45.7
unnamed: Q120.3 (D), R173.1, R174.1
unnamed: Q99.1 (G), Q120.1 (G), R169.1, R194.2, U52.7
unnamed: R45.2, R46.1, U10.1
unnamed: R66.2, R67.1, U17.1
unnamed: R87.2, R88.1, U24.1
unnamed: R108.2, R109.1, U31.1
unnamed: R129.2, R130.1, U38.1
unnamed: R150.2, R151.1, U45.1
unnamed: R171.2, R172.1, U52.1
unnamed: R42.2, U8.3 (SET)
unnamed: R45.1, U10.3 (+), U11.12 (P0W)
unnamed: R188.1, R196.1, R204.2, U10.5 (+)
unnamed: C17.2, R46.2, U10.6 (-)
unnamed: R40.1, R41.1, U11.10 (P1A)
unnamed: U8.1 (IN), U11.9 (P1W)
unnamed: R66.1, U12.12 (P0W), U17.3 (+)
unnamed: R61.1, R62.1, U12.10 (P1A)
unnamed: U12.9 (P1W), U15.1 (IN)
unnamed: R63.2, U15.3 (SET)
unnamed: R189.1, R197.1, R205.2, U17.5 (+)
unnamed: C25.2, R67.2, U17.6 (-)
unnamed: R87.1, U18.12 (P0W), U24.3 (+)
unnamed: R82.1, R83.1, U18.10 (P1A)
unnamed: U18.9 (P1W), U22.1 (IN)
unnamed: R108.1, U19.12 (P0W), U31.3 (+)
unnamed: R103.1, R104.1, U19.10 (P1A)
unnamed: U19.9 (P1W), U29.1 (IN)
unnamed: R84.2, U22.3 (SET)
unnamed: R190.1, R198.1, R206.2, U24.5 (+)
unnamed: C33.2, R88.2, U24.6 (-)
unnamed: R129.1, U25.12 (P0W), U38.3 (+)
unnamed: R124.1, R125.1, U25.10 (P1A)
unnamed: U25.9 (P1W), U36.1 (IN)
unnamed: R150.1, U26.12 (P0W), U45.3 (+)
unnamed: R145.1, R146.1, U26.10 (P1A)
unnamed: U26.9 (P1W), U43.1 (IN)
unnamed: R105.2, U29.3 (SET)
unnamed: R191.1, R199.1, R207.2, U31.5 (+)
unnamed: C41.2, R109.2, U31.6 (-)
unnamed: R171.1, U32.12 (P0W), U52.3 (+)
unnamed: R166.1, R167.1, U32.10 (P1A)
unnamed: U32.9 (P1W), U50.1 (IN)
unnamed: R126.2, U36.3 (SET)
unnamed: R192.1, R200.1, R208.2, U38.5 (+)
unnamed: C49.2, R130.2, U38.6 (-)
unnamed: R147.2, U43.3 (SET)
unnamed: R193.1, R201.1, R209.2, U45.5 (+)
unnamed: C57.2, R151.2, U45.6 (-)
unnamed: R168.2, U50.3 (SET)
unnamed: R194.1, R202.1, R210.2, U52.5 (+)
unnamed: C65.2, R172.2, U52.6 (-)

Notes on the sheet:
comparator with hysteresis
Connector
output with overcurrent protection
C_{mem}
PWM generator
discharge transistor
unused
weights
summation point for synaptic input currents
indicator LED
RC delay circuit determines spike duration
variable spiking threshold
Axon
variable leak resistor PWM controlled
inhibitory
Synapses
excitatory
U_{F}=2.3V

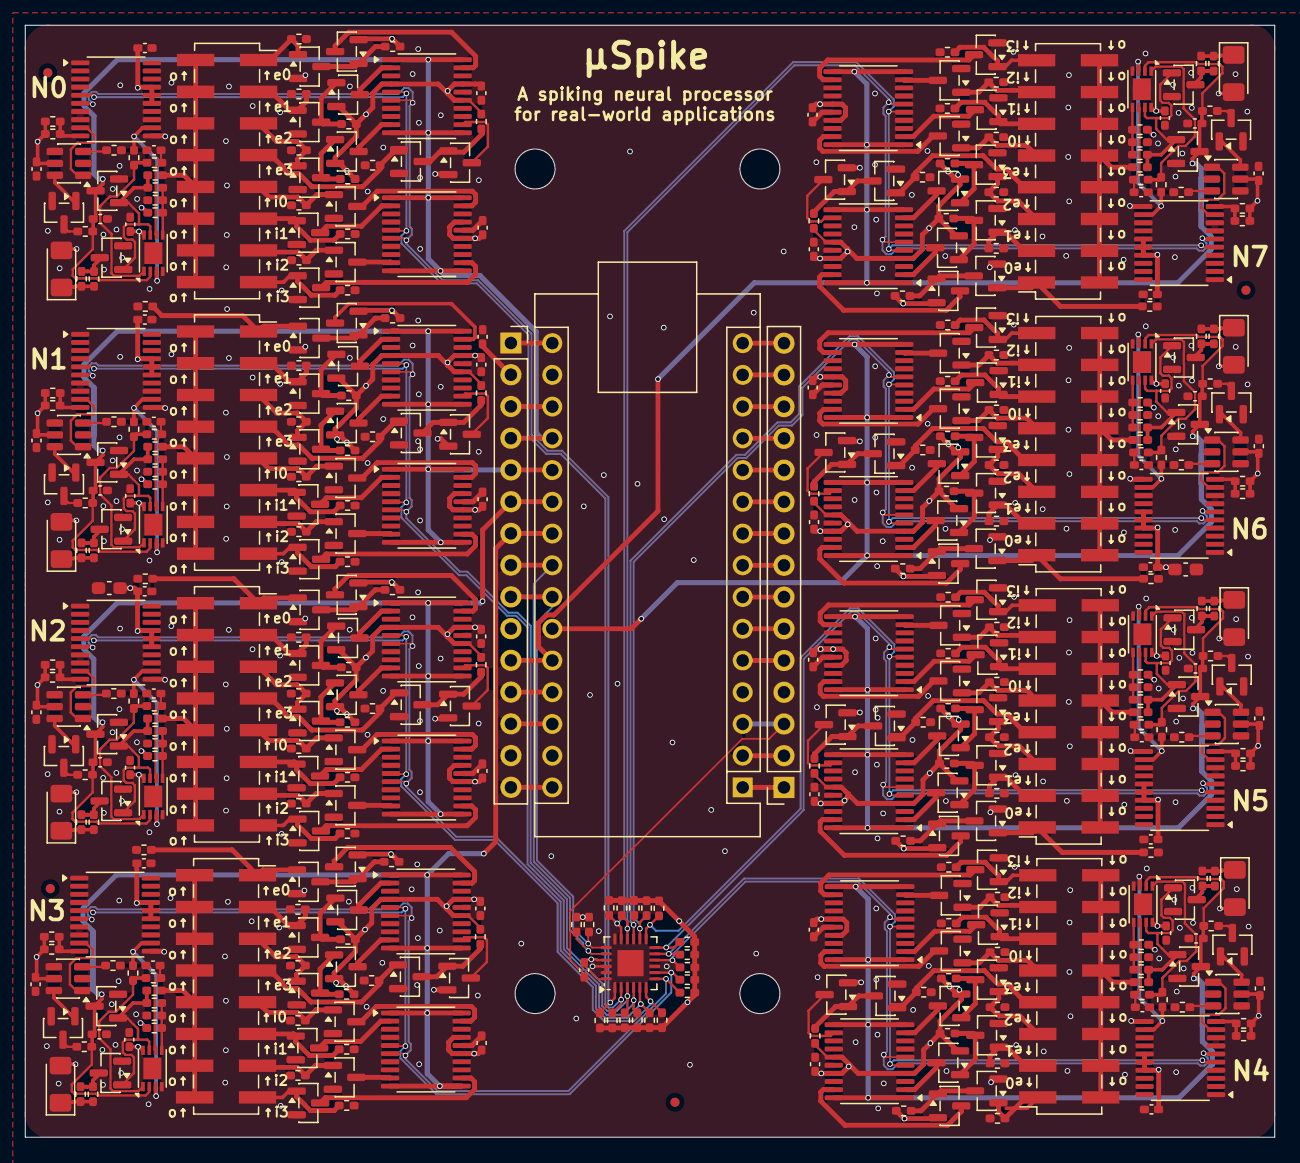
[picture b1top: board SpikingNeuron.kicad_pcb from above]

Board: 4 copper layers, 100.0 x 89.0 mm, 458 parts (0 on the bottom side), 311 nets.
